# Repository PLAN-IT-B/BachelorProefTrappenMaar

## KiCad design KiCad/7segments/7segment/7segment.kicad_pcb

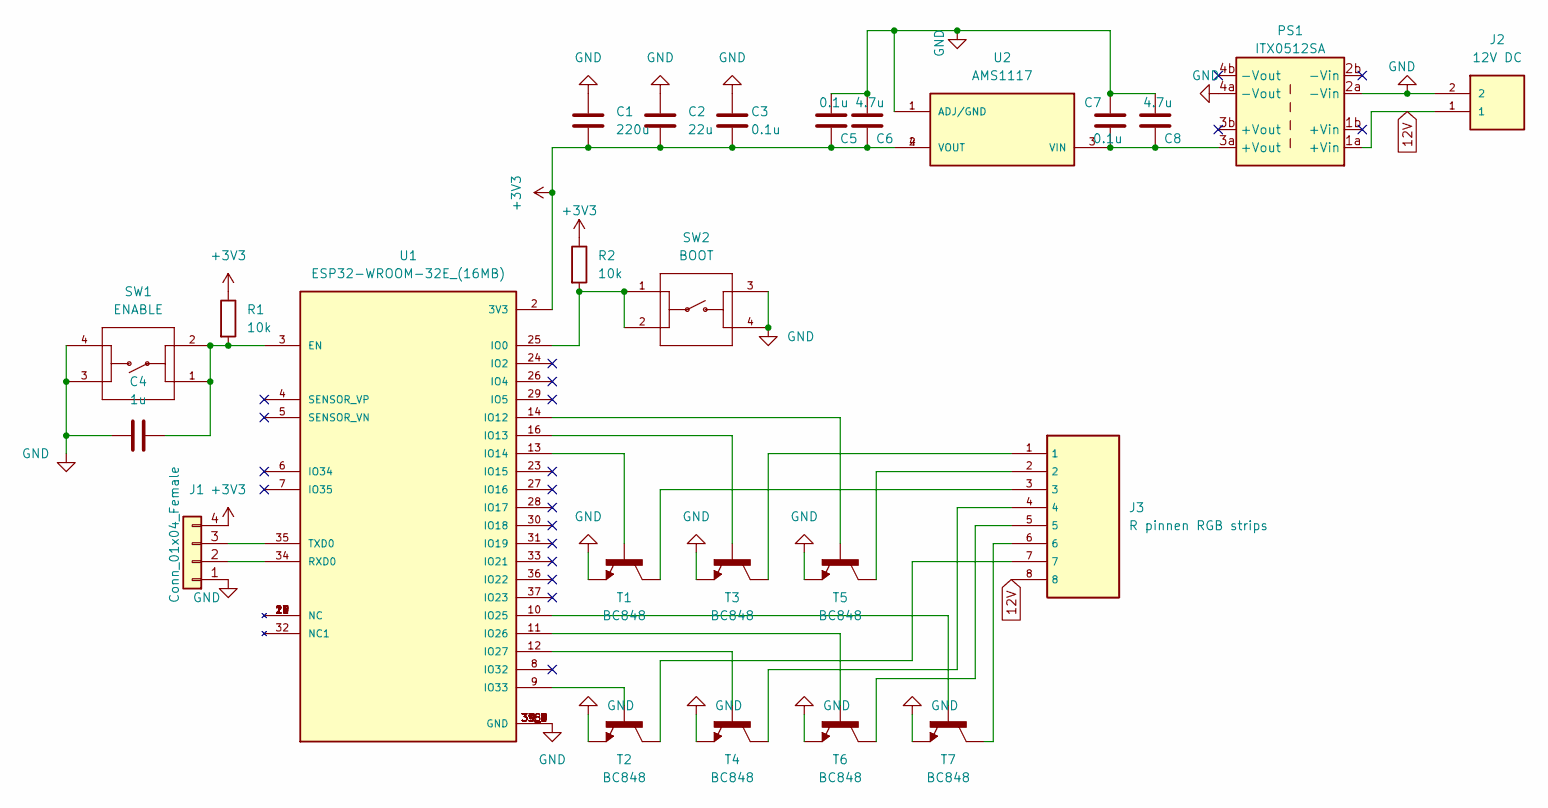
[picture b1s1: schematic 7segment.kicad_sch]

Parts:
C1: 220u; C_0805_2012Metric
C2: 22u; C_0805_2012Metric
C3, C5, C7: 0.1u; C_0805_2012Metric
C4: 1u; C_0805_2012Metric
C6, C8: 4.7u; C_0805_2012Metric
J1: Conn_01x04_Female; PinHeader_1x04_P2.54mm_Vertical
J2: 12V DC; TE_282841-2
J3: R pinnen RGB strips; TE_282841-8
PS1: ITX0512SA; Buck Converter
R1, R2: 10k; R_0805_2012Metric
SW1: ENABLE; SW_1825910-6-4
SW2: BOOT; SW_1825910-6-4
T1, T2, T3, T4, T5, T6, T7: BC848; SOT23
U1: ESP32-WROOM-32E_(16MB); XCVR_ESP32-WROOM-32E_(16MB); PARTREV 1.4
U2: AMS1117; SOT229P700X180-4N; PARTREV N/A

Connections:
12V: J2.1, J3.8, PS1.1a (+Vin)
+3V3: C1.1, C2.1, C3.1, C5.1, C6.1, J1.4, R1.1, R2.1, U1.2 (3V3), U2.2 (VOUT), U2.4 (VOUT)
GND: C1.2, C2.2, C3.2, C4.1, C5.2, C6.2, C7.1, C8.2, J1.1, J2.2, PS1.2a (-Vin), PS1.4a (-Vout), SW1.3, SW1.4, SW2.3, SW2.4, T1.2, T2.2, T3.2, T4.2, T5.2, T6.2, T7.2, U1.1 (GND), U1.15 (GND), U1.38 (GND), U1.39_1 (GND), U1.39_2 (GND), U1.39_3 (GND), U1.39_4 (GND), U1.39_5 (GND), U1.39_6 (GND), U1.39_7 (GND), U1.39_8 (GND), U1.39_9 (GND), U2.1 (ADJ/GND)
unnamed: C4.2, R1.2, SW1.1, SW1.2, U1.3 (EN)
unnamed: C7.2, C8.1, PS1.3a (+Vout), U2.3 (VIN)
unnamed: J1.2, U1.34 (RXD0)
unnamed: J1.3, U1.35 (TXD0)
unnamed: J3.1, T3.3
unnamed: J3.2, T5.3
unnamed: J3.3, T1.3
unnamed: J3.4, T4.3
unnamed: J3.5, T6.3
unnamed: J3.6, T7.3
unnamed: J3.7, T2.3
unnamed: R2.2, SW2.1, SW2.2, U1.25 (IO0)
unnamed: T1.1, U1.13 (IO14)
unnamed: T2.1, U1.9 (IO33)
unnamed: T3.1, U1.16 (IO13)
unnamed: T4.1, U1.12 (IO27)
unnamed: T5.1, U1.14 (IO12)
unnamed: T6.1, U1.11 (IO26)
unnamed: T7.1, U1.10 (IO25)

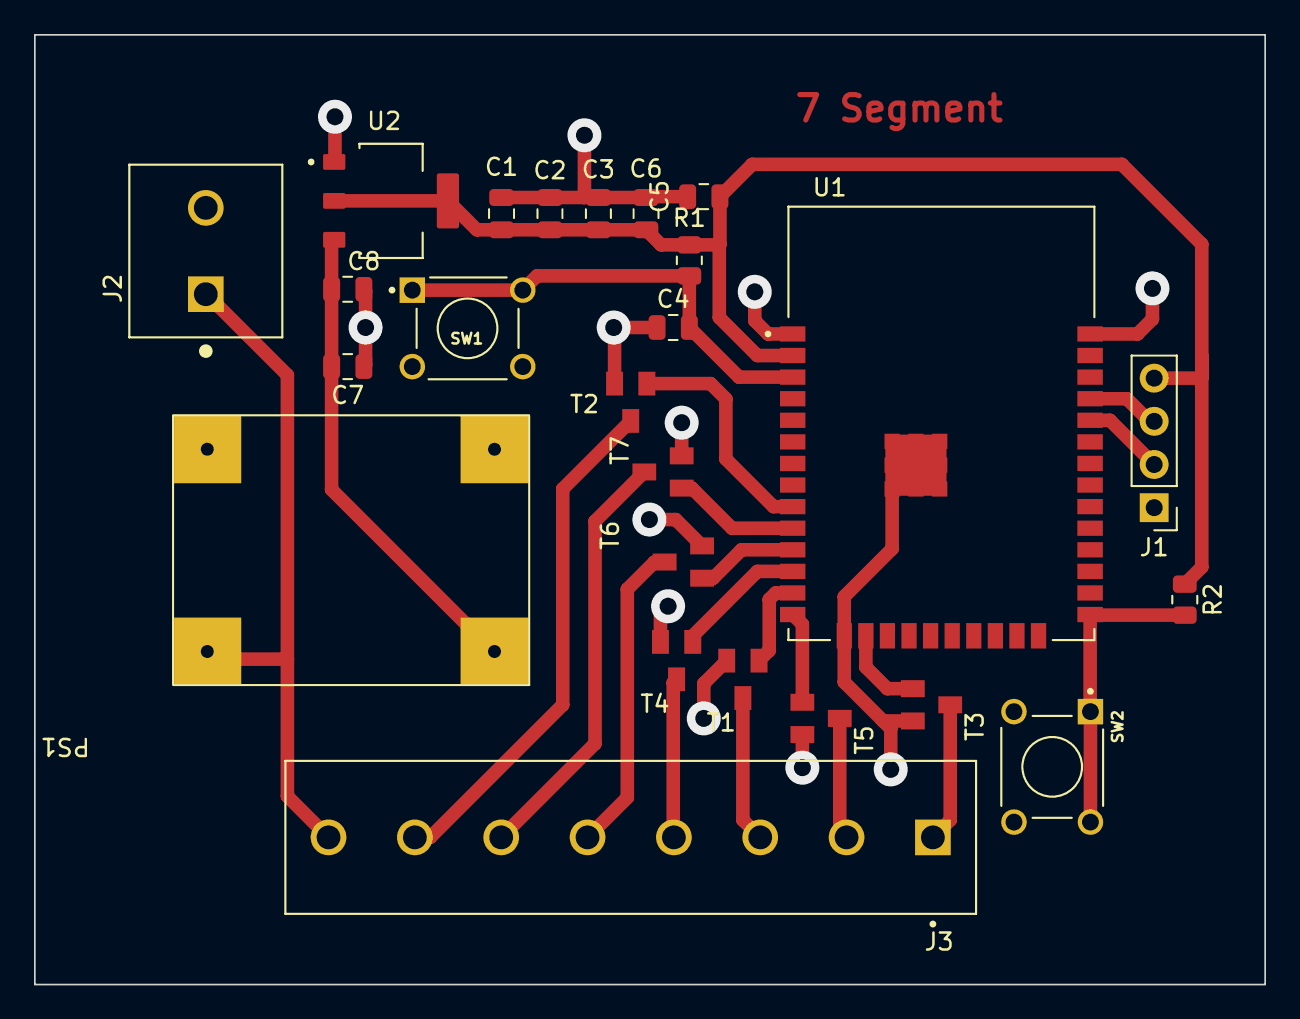
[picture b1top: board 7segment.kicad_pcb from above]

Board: 2 copper layers, 72.4 x 55.9 mm, 25 parts (0 on the bottom side), 22 nets.

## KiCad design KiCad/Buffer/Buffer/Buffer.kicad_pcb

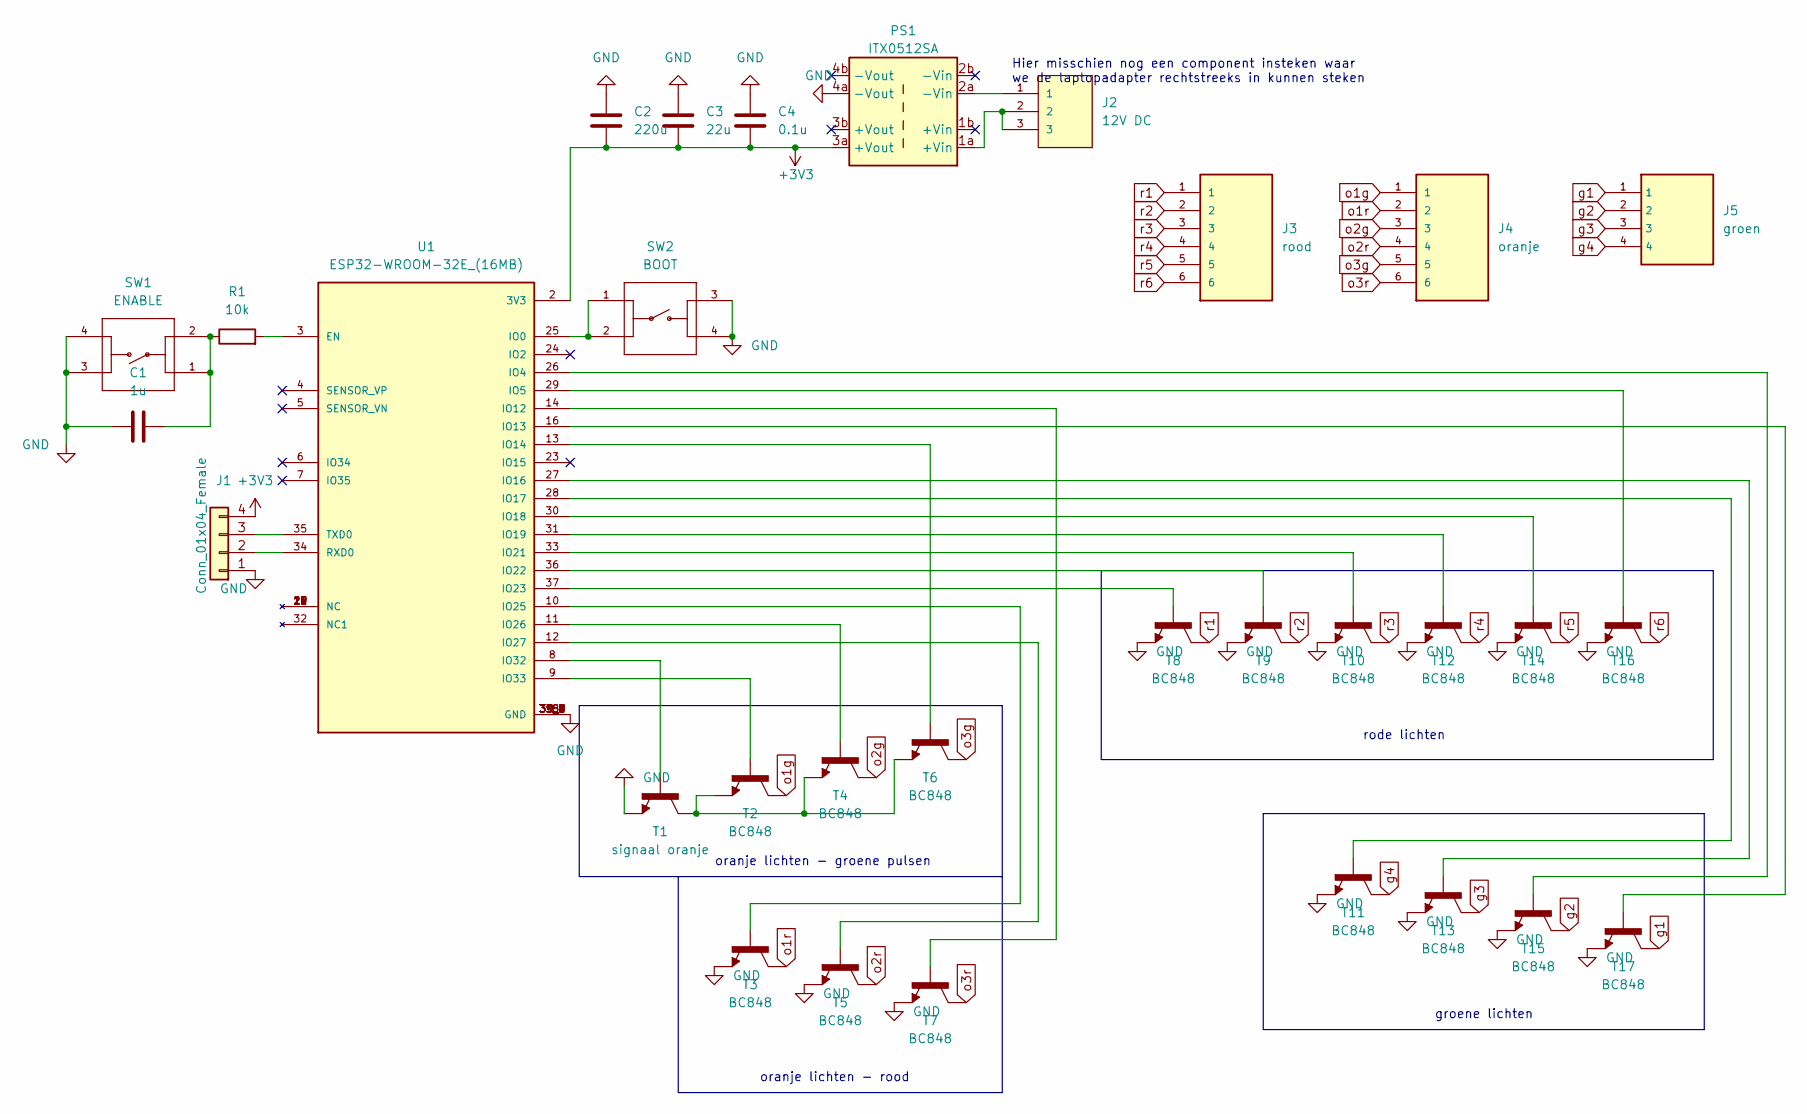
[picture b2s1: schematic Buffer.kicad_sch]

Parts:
C1: 1u; C_0805_2012Metric
C2: 220u; C_0805_2012Metric
C3: 22u; C_0805_2012Metric
C4: 0.1u; C_0805_2012Metric
J1: Conn_01x04_Female; PinHeader_1x04_P2.54mm_Vertical
J2: 12V DC; TE_282841-3
J3: rood; TE_282841-6
J4: oranje; TE_282841-6
J5: groen; TE_282841-4
PS1: ITX0512SA; Buck Converter
R1: 10k
SW1: ENABLE; SW_1825910-6-4
SW2: BOOT; SW_1825910-6-4
T1: signaal oranje; SOT23
T2, T3, T4, T5, T6, T7, T8, T9, T10, T11, T12, T13, T14, T15, T16, T17: BC848; SOT23
U1: ESP32-WROOM-32E_(16MB); XCVR_ESP32-WROOM-32E_(16MB); PARTREV 1.4

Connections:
+3V3: C2.1, C3.1, C4.1, J1.4, PS1.3a (+Vout), U1.2 (3V3)
GND: C1.1, C2.2, C3.2, C4.2, J1.1, PS1.4a (-Vout), SW1.3, SW1.4, SW2.3, SW2.4, T1.2, T3.2, T5.2, T7.2, T8.2, T9.2, T10.2, T11.2, T12.2, T13.2, T14.2, T15.2, T16.2, T17.2, U1.1 (GND), U1.15 (GND), U1.38 (GND), U1.39_1 (GND), U1.39_2 (GND), U1.39_3 (GND), U1.39_4 (GND), U1.39_5 (GND), U1.39_6 (GND), U1.39_7 (GND), U1.39_8 (GND), U1.39_9 (GND)
unnamed: C1.2, R1.1, SW1.1, SW1.2
unnamed: J1.2, U1.34 (RXD0)
unnamed: J1.3, U1.35 (TXD0)
unnamed: J2.1, PS1.2a (-Vin)
unnamed: J2.2, J2.3, PS1.1a (+Vin)
unnamed: R1.2, U1.3 (EN)
unnamed: SW2.1, SW2.2, U1.25 (IO0)
unnamed: T1.1, U1.8 (IO32)
unnamed: T1.3, T2.2, T4.2, T6.2
unnamed: T2.1, U1.9 (IO33)
unnamed: T3.1, U1.10 (IO25)
unnamed: T4.1, U1.11 (IO26)
unnamed: T5.1, U1.12 (IO27)
unnamed: T6.1, U1.13 (IO14)
unnamed: T7.1, U1.14 (IO12)
unnamed: T8.1, U1.37 (IO23)
unnamed: T9.1, U1.36 (IO22)
unnamed: T10.1, U1.33 (IO21)
unnamed: T11.1, U1.28 (IO17)
unnamed: T12.1, U1.31 (IO19)
unnamed: T13.1, U1.27 (IO16)
unnamed: T14.1, U1.30 (IO18)
unnamed: T15.1, U1.26 (IO4)
unnamed: T16.1, U1.29 (IO5)
unnamed: T17.1, U1.16 (IO13)
g1: J5.1, T17.3
g2: J5.2, T15.3
g3: J5.3, T13.3
g4: J5.4, T11.3
o1g: J4.1, T2.3
o1r: J4.2, T3.3
o2g: J4.3, T4.3
o2r: J4.4, T5.3
o3g: J4.5, T6.3
o3r: J4.6, T7.3
r1: J3.1, T8.3
r2: J3.2, T9.3
r3: J3.3, T10.3
r4: J3.4, T12.3
r5: J3.5, T14.3
r6: J3.6, T16.3

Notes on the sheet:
rode lichten
oranje lichten - groene pulsen
groene lichten
Hier misschien nog een component insteken waar we de laptopadapter rechtstreeks in kunnen steken
oranje lichten - rood

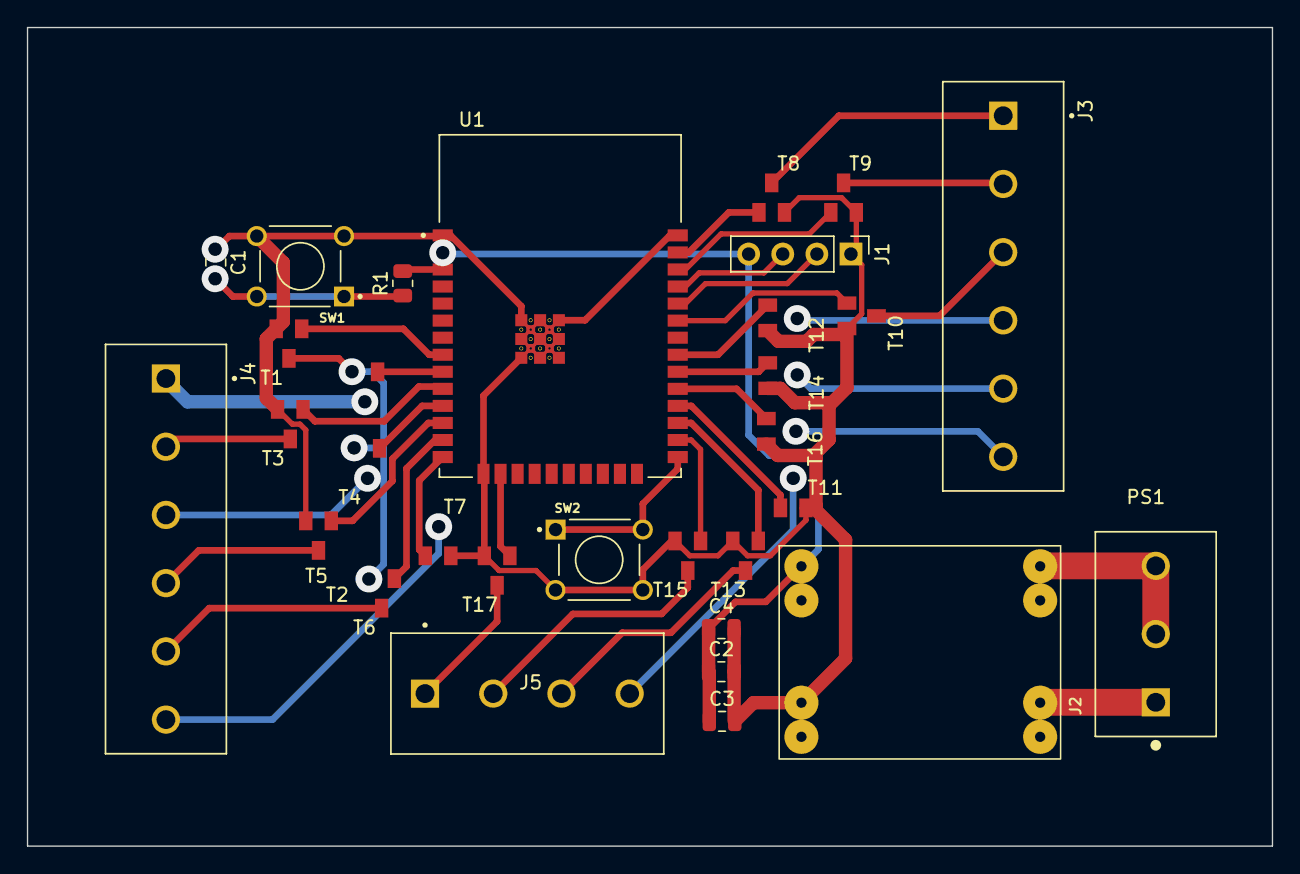
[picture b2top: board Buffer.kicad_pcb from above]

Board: 2 copper layers, 92.7 x 61.0 mm, 31 parts (0 on the bottom side), 43 nets.

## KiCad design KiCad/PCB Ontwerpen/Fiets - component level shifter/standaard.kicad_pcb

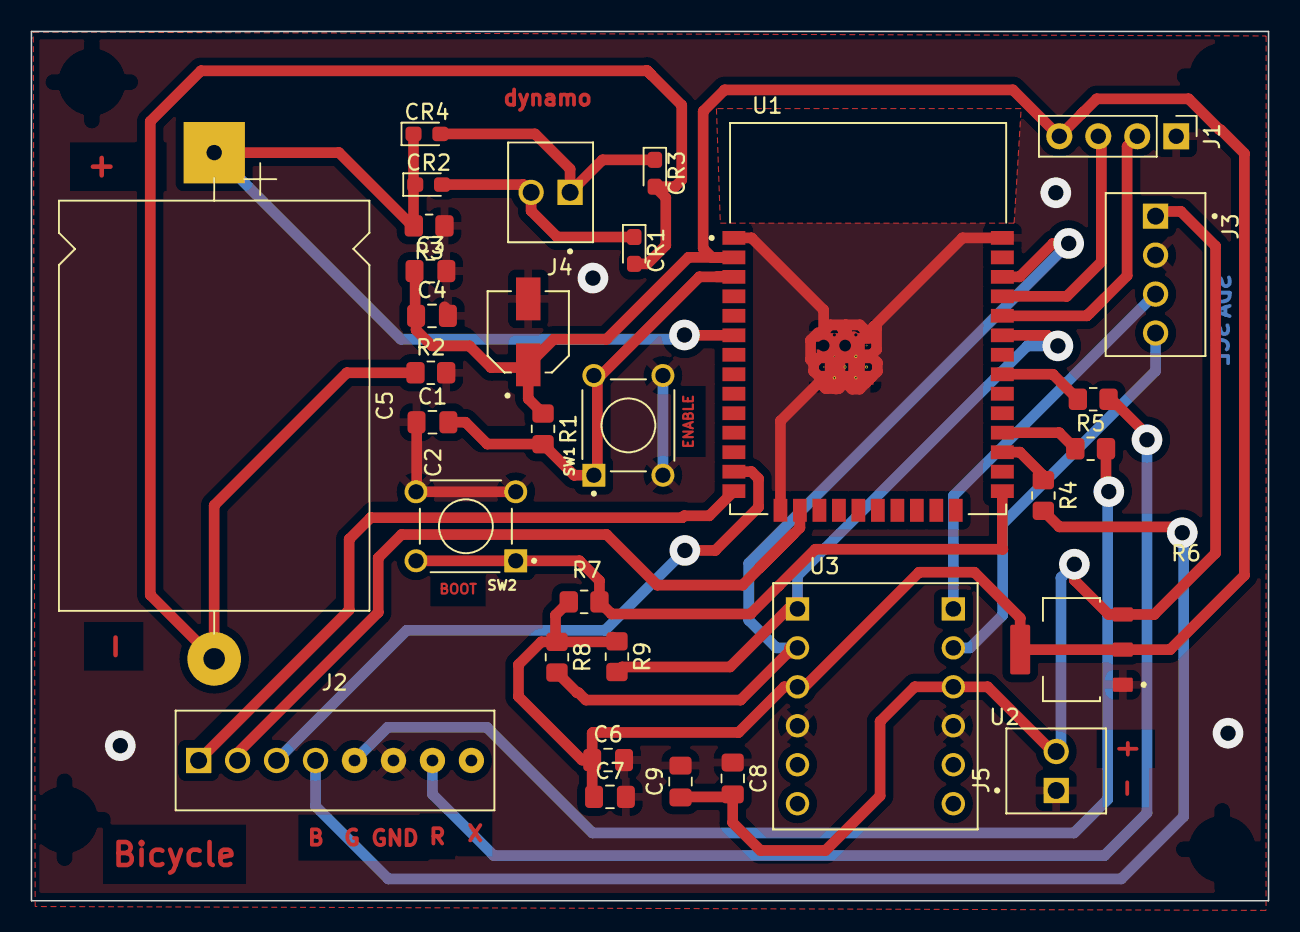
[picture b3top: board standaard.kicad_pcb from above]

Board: 2 copper layers, 80.6 x 56.7 mm, 32 parts (0 on the bottom side), 24 nets.

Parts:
C1: 1u; C_0805_2012Metric_Pad1.18x1.45mm_HandSolder
C2: 220u; CAP_EEE0JA101WR
C3: 22u; C_0805_2012Metric_Pad1.18x1.45mm_HandSolder
C4, C6, C8: 0.1u; C_0805_2012Metric_Pad1.18x1.45mm_HandSolder
C5: 1000µ; CP_Axial_L26.5mm_D20.0mm_P33.00mm_Horizontal
C7, C9: 4.7u; C_0805_2012Metric_Pad1.18x1.45mm_HandSolder
CR1, CR2, CR3, CR4: 1N4148W-TP; D_0603_1608Metric_Pad1.05x0.95mm_HandSolder
J1: Conn_01x04_Female; PinHeader_1x04_P2.54mm_Vertical
J2: R pinnen RGB strips; TE_1546215-8
J3: 282837-4; TE_1546215-4
J4, J5: 282841-2; TE_1546215-2
R1, R7, R8, R9: 10k; R_0805_2012Metric_Pad1.20x1.40mm_HandSolder
R2: 560; R_0805_2012Metric_Pad1.20x1.40mm_HandSolder
R3: 120; R_0805_2012Metric_Pad1.20x1.40mm_HandSolder
R4, R5, R6: 82; R_0805_2012Metric_Pad1.20x1.40mm_HandSolder
SW1: ENABLE; SW_1825910-6-4
SW2: BOOT; SW_1825910-6-4
U1: ESP32-WROOM-32E_(16MB); XCVR_ESP32-WROOM-32E_(16MB)
U2: AMS1117; SOT229P700X180-4N
U3: BOB-12009; CONV_BOB-12009

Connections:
+3V3: C2.1, C3.1, C4.1, C6.1, C7.1, J1.4, R1.1, R7.1, R8.1, R9.1, U1.2 (3V3), U2.2 (VOUT), U2.4 (VOUT), U3.LV
+5V: C8.2, C9.1, J3.1, J5.2, U2.3 (VIN), U3.HV
GND: C1.1, C2.2, C3.2, C4.2, C6.2, C7.2, C8.1, C9.2, J1.1, J2.6, J3.2, J5.1, R2.2, R3.1, SW1.3, SW1.4, SW2.3, SW2.4, U1.1 (GND), U1.15 (GND), U1.38 (GND), U1.39_1 (GND), U1.39_2 (GND), U1.39_3 (GND), U1.39_4 (GND), U1.39_5 (GND), U1.39_6 (GND), U1.39_7 (GND), U1.39_8 (GND), U1.39_9 (GND), U2.1 (ADJ/GND), U3.GND_1 (GND), U3.GND_2 (GND)
unnamed: C1.2, R1.2, SW1.1, SW1.2, U1.3 (EN)
unnamed: C5.1, CR2.1, CR4.1, R3.2, U1.6 (IO34)
unnamed: C5.2, CR1.2, CR3.2, R2.1
unnamed: CR1.1, CR2.2, J4.2
unnamed: CR3.1, CR4.2, J4.1
unnamed: J1.2, U1.34 (RXD0)
unnamed: J1.3, U1.35 (TXD0)
unnamed: J2.1, U1.14 (IO12)
unnamed: J2.2, U1.16 (IO13)
unnamed: J2.3, U1.13 (IO14)
unnamed: J2.4, R4.2
unnamed: J2.5, R5.2
unnamed: J2.7, R6.2
unnamed: J3.3, U3.HV1
unnamed: J3.4, U3.HV2
unnamed: R4.1, U1.27 (IO16)
unnamed: R5.1, U1.28 (IO17)
unnamed: R6.1, U1.31 (IO19)
unnamed: R7.2, SW2.1, SW2.2, U1.25 (IO0)
unnamed: R8.2, U1.36 (IO22), U3.LV2
unnamed: R9.2, U1.33 (IO21), U3.LV1

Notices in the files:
parts and their libraries:
COPYRIGHT: Copyright (C) 2018 Accelerated Designs. All rights reserved
